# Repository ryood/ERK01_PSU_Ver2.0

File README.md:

# ERK01_PSU_Ver2.0
84 HP, 2-tier Eurorack.
Dual 12 / +5V power supply included.

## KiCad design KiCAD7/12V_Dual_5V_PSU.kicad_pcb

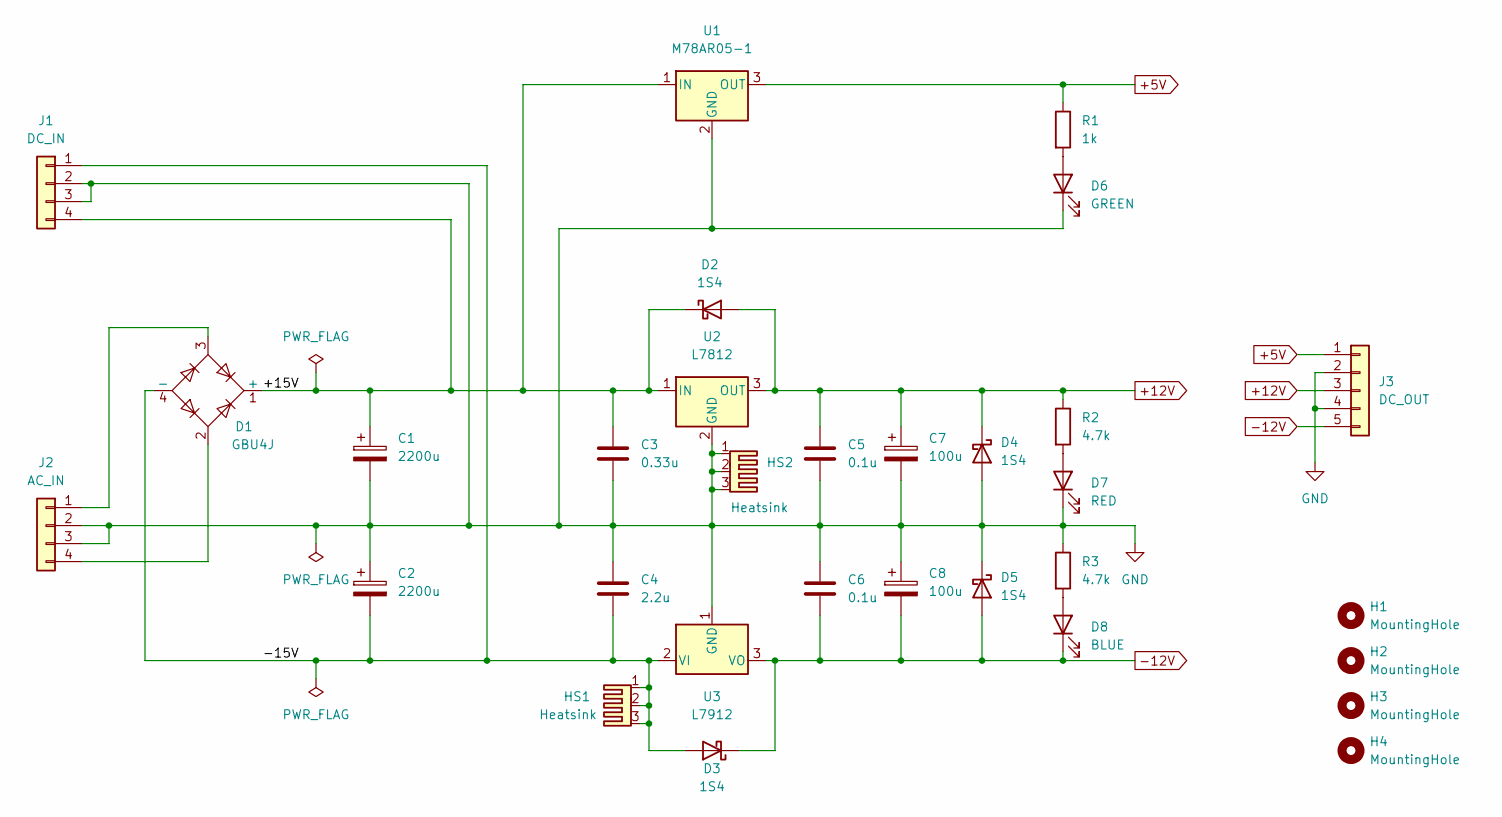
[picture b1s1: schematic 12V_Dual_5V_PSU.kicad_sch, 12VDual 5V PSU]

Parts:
C1, C2: 2200u; CP_Radial_D16.0mm_P7.50mm
C3: 0.33u; C_Disc_D3.0mm_W1.6mm_P2.50mm
C4: 2.2u; C_Disc_D4.3mm_W1.9mm_P5.00mm
C5, C6: 0.1u; C_Disc_D3.0mm_W1.6mm_P2.50mm
C7, C8: 100u; CP_Radial_D6.3mm_P2.50mm
D1: GBU4J; Diode_Bridge_Vishay_GBU
D2, D3, D4, D5: 1S4; D_DO-35_SOD27_P7.62mm_Horizontal
D6: GREEN; LED_D3.0mm
D7: RED; LED_D3.0mm
D8: BLUE; LED_D3.0mm
H1, H2, H3, H4: MountingHole; MountingHole_3.2mm_M3
HS1, HS2: Heatsink; Heatsink_30PC030
J1: DC_IN; JST_XH_B4B-XH-A_1x04_P2.50mm_Vertical
J2: AC_IN; JST_XH_B4B-XH-A_1x04_P2.50mm_Vertical
J3: DC_OUT; JST_XH_B5B-XH-A_1x05_P2.50mm_Vertical
R1: 1k; R_Axial_DIN0207_L6.3mm_D2.5mm_P10.16mm_Horizontal
R2, R3: 4.7k; R_Axial_DIN0207_L6.3mm_D2.5mm_P10.16mm_Horizontal
U1: M78AR05-1; M78AR-1
U2: L7812; TO-220F-3_Vertical
U3: L7912; TO-220F-3_Vertical

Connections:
+5V: J3.1, R1.1, U1.3 (OUT)
+12V: C5.1, C7.1, D2.2 (A), D4.1 (K), J3.3, R2.1, U2.3 (OUT)
-12V: C6.2, C8.2, D3.1 (K), D5.2 (A), D8.1 (K), J3.5, U3.3 (VO)
/+15V: C1.1, C3.1, D1.1 (+), D2.1 (K), J1.4, U1.1 (IN), U2.1 (IN)
/-15V: C2.2, C4.2, D1.4 (-), D3.2 (A), HS1.1, HS1.2, HS1.3, J1.1, U3.2 (VI)
GND: C1.2, C2.1, C3.2, C4.1, C5.2, C6.1, C7.2, C8.1, D4.2 (A), D5.1 (K), D6.1 (K), D7.1 (K), HS2.1, HS2.2, HS2.3, J1.2, J1.3, J2.2, J2.3, J3.2, J3.4, R3.1, U1.2 (GND), U2.2 (GND), U3.1 (GND)
unnamed: D1.2, J2.4
unnamed: D1.3, J2.1
unnamed: D6.2 (A), R1.2
unnamed: D7.2 (A), R2.2
unnamed: D8.2 (A), R3.2

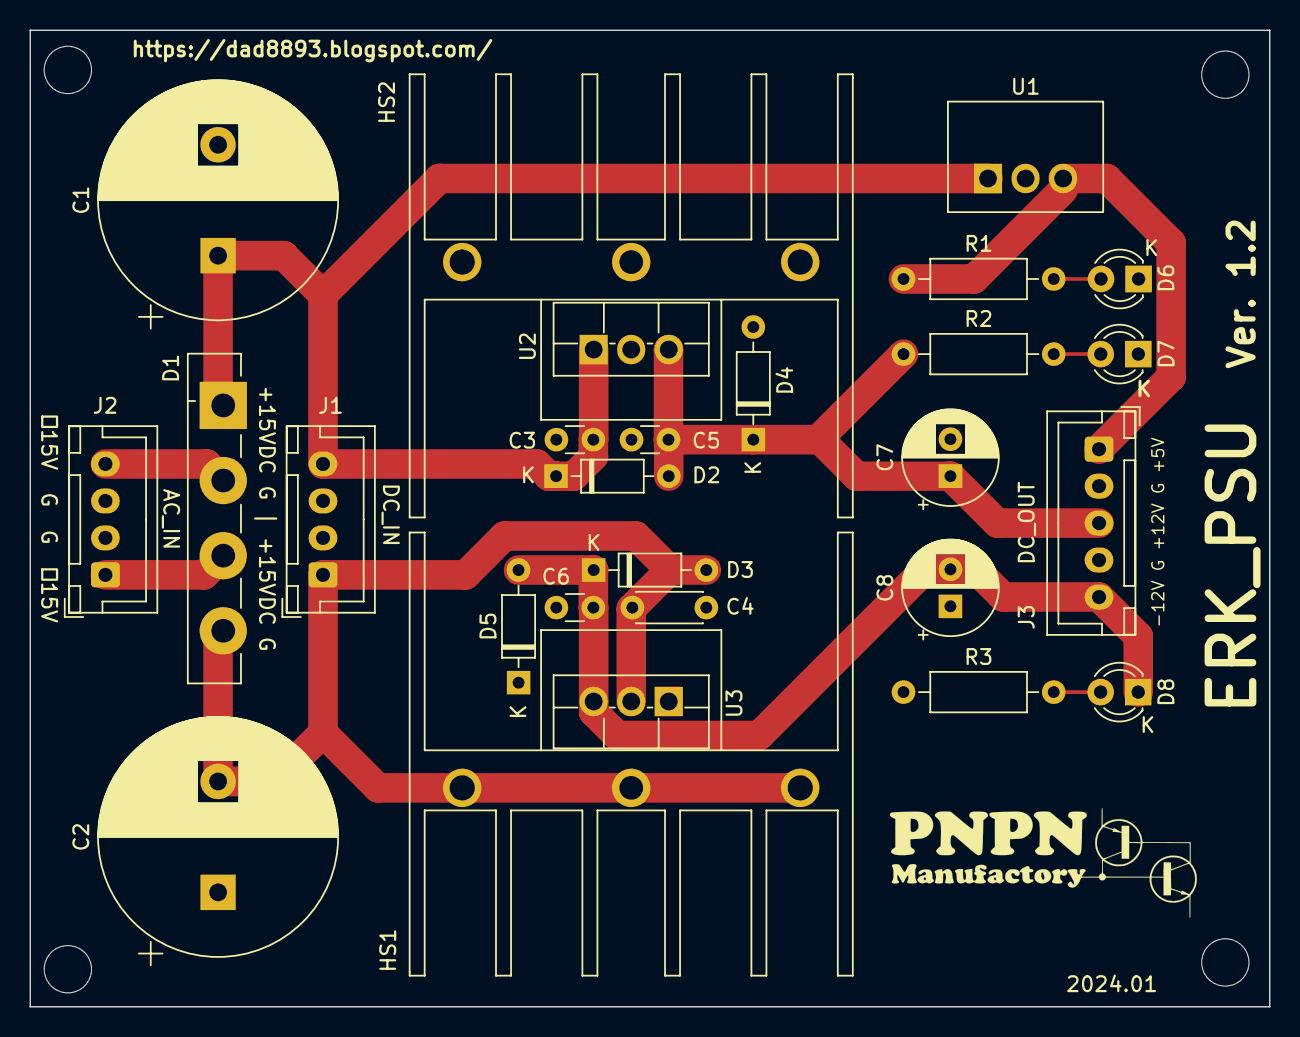
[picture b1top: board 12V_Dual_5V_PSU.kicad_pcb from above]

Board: 2 copper layers, 83.8 x 66.0 mm, 31 parts (0 on the bottom side), 11 nets.

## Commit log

2023-12-29 Add .md
